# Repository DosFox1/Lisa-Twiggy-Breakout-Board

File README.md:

# Lisa-Twiggy-Breakout-Board
A fork of Roland Juno's original Lisa breakout board - now with Twiggy!

# So... What is it? 
This is a variant of RolandJunos original Lisa breakout board (https://github.com/RolandJuno/Lisa_Breakout), that includes an additional connector for the Lisa LITE. 
Adding the Lisa LITE connector will allow for 400K Floppy Drives to be connected to a Lisa.
This is because the Lisa LITE generates a PWM signal for the main drive motor in the 400K floppy drive. 
In a Macintosh, this PWM signal is generated by the ASG and audio interface! (I mean, I guess it's all PWM signals).

However, 800K drives and Floppy Emu generate their own PWM signal - so that pin is usually left disconnected. 
As a result, you can use a passive adapter for those drives.

Note, in the surprising event that you have an actual Twiggy Drive, please note this probably will not work.
This is because to two signals (sense and read) are tied together for the 800K drive. I felt a bit lazy and didn't add a way to keep these separate. 
If you have a Twiggy, cut and strap I guess? 

# Engineers Notes
The BOM remains the same as the original breakout board, except for the addition of a 26 pin shrouded connector for the Twiggy pinout.

**IMPORTANT:**

Do NOT connect a Twiggy/Lisa LITE at the same time as a Sony Drive. They share the same enable lines, and bad stuff (TM) is likely to happen. 
So don't do that. 

**Errata and other notes:**

* I've cleaned up some of the tracks and added thermal relief for soldering. 
* The errata for the 7905 footprint has been fixed (and added some silk to make sure the polarity is right!).
* AGND is also now connected to normal DGND, so no jumper is needed.
* Mounting holes have now been added (three in total), which are positioned in a line on the board. This will help with case building.
* To help with case building, the included SVGs are 1:1 scale to the actual board, meaning they can be imported into your favourite CAD program to help build a case around it.

**NOTE - This is Entirely Untested. Proceed With Caution**

It's best practise to power thsi adapter board with a bare (I.E, no IC's present) motherboard for intial testing.

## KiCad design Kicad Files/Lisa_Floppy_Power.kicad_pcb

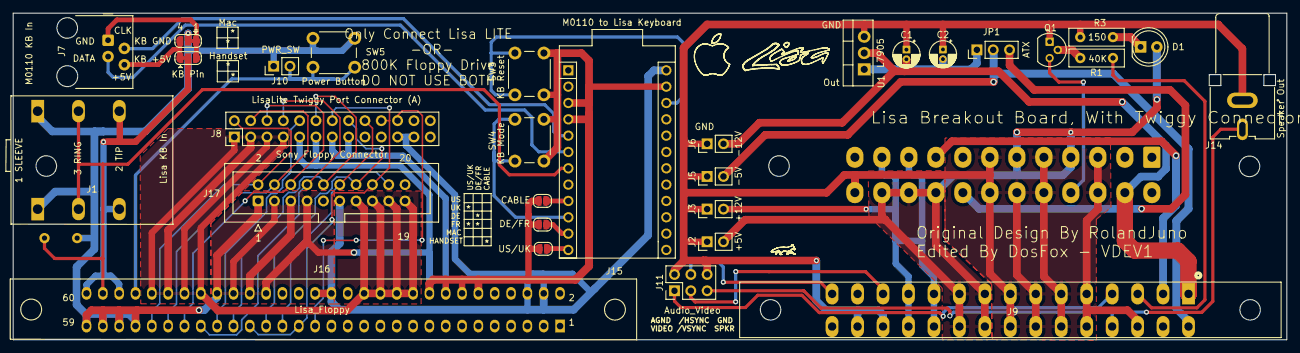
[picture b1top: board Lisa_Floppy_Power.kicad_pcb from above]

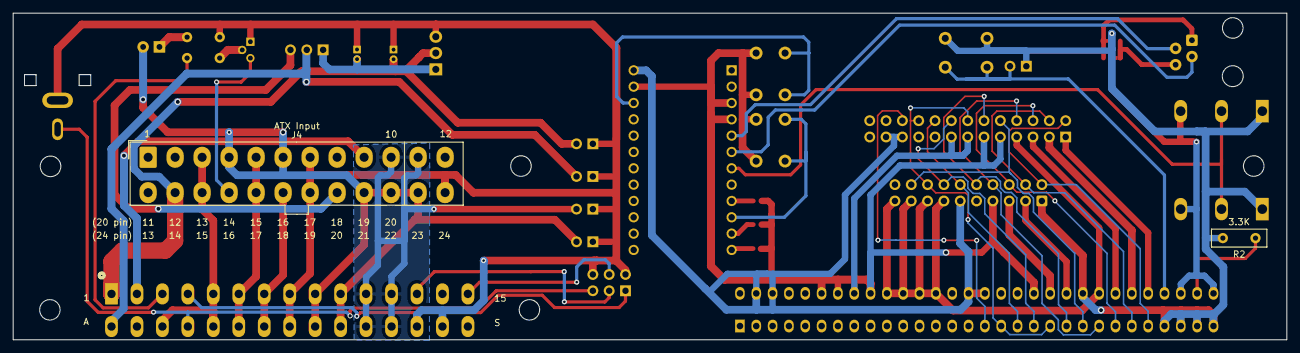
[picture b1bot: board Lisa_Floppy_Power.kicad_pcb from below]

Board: 2 copper layers, 198.1 x 50.8 mm, 32 parts (2 on the bottom side), 41 nets.

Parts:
C1, C2: 0.1uf; CP_Radial_D4.0mm_P1.50mm
D1: LED; LED_D5.0mm
J1: Lisa KB In; 0.25IN_STEREO_HEADPHONE_JACK
J2: +5V; PinHeader_1x02_P2.54mm_Vertical
J3: +12V; PinHeader_1x02_P2.54mm_Vertical
J4: ATX-24; Molex_Mini-Fit_Jr_5566-24A_2x12_P4.20mm_Vertical
J5: -5V; PinHeader_1x02_P2.54mm_Vertical
J6: -12V; PinHeader_1x02_P2.54mm_Vertical
J7: Mac_Plus_RJ9-4P4C; RJ9_Evercom_5301-440xxx_Horizontal
J8: LisaLite Twiggy Port Connector (A); PinHeader_2x13_P2.54mm_Vertical
J9: Lisa_Power_Video_Sound_Edge; Lisa Motherboard Power Edge
J10: PWR_SW; PinHeader_1x02_P2.54mm_Vertical
J11: Audio_Video; PinHeader_2x03_P2.54mm_Vertical
J14: Speaker Out; CUI_RCJ-047
J15: Arduino_Pro_Micro_5V_16MHz; Sparkfun_Pro_Micro
J16: Lisa_Floppy; 1-5530841-8_TE_CONN_60_DUAL_EDGE
J17: Sony Floppy Connector; IDC-Header_2x10_P2.54mm_Vertical
JP1: -5V_Selector; PinHeader_1x03_P2.54mm_Vertical
JP2: KB +5V; SolderJumper-3_P1.3mm_Bridged12_RoundedPad1.0x1.5mm
JP3: KB GND; SolderJumper-3_P1.3mm_Bridged12_RoundedPad1.0x1.5mm
JP4: US/UK; SolderJumper-2_P1.3mm_Open_RoundedPad1.0x1.5mm
JP5: DE/FR; SolderJumper-2_P1.3mm_Open_RoundedPad1.0x1.5mm
JP6: CABLE; SolderJumper-2_P1.3mm_Open_RoundedPad1.0x1.5mm
Q1: 2N4401BU; TO-92
R1: 40K; R_Box_L8.4mm_W2.5mm_P5.08mm
R2: 3.3K; R_Box_L8.4mm_W2.5mm_P5.08mm
R3: 150; R_Box_L8.4mm_W2.5mm_P5.08mm
SW3: KB Reset; SW_PUSH_6mm
SW4: KB Mode; SW_PUSH_6mm
SW5: Power Button; SW_PUSH_6mm
U1: L7905; TO-220-3_Vertical

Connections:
+5V: D1.2 (A), J2.2, J4.4 (+5V), J4.6 (+5V), J4.21 (+5V), J4.22 (+5V), J4.23 (+5V), J9.9, J9.10, J9.K, J9.L
+5VSB: J4.9 (+5VSB), J9.2
+5V_L: J8.21 (+5V), J8.23 (+5V), J15.24 (RAW), J16.4, J16.6, J16.30, J16.32, J17.11
+5V_L1: J1.2 (T), J16.56, J16.60, JP2.2 (C)
+12V-L: J8.1 (+12V), J8.3 (+12V), J8.5 (+12V), J8.7 (+12V), J16.20, J16.22, J16.24, J16.26, J16.46, J16.48, J16.50, J16.52, J17.13, J17.15, J17.17, J17.19
+12V-R: J3.2, J4.10 (+12V), J4.11 (+12V), J9.11, J9.12, J9.M, J9.N
-5V: J5.2, J9.A, JP1.2 (C)
-5V_7905: C2.2, JP1.1 (A), U1.1 (GND)
-5V_ATX: J4.20 (-5V), JP1.3 (B)
-12V: C1.2, J4.14 (-12V), J6.2, J9.1, U1.2 (VI)
CABLE: J15.9 (~D6/A7), JP6.2 (B)
DE/FR: J15.11 (D8/A8), JP5.2 (B)
GND-L: J1.1 (S), J8.9 (GND), J8.11 (GND), J8.13 (GND), J8.15 (GND), J10.1, J15.3 (GND), J15.4 (GND), J15.23 (GND), J16.12, J16.14, J16.16, J16.18, J16.38, J16.40, J16.42, J16.44, J16.53, J16.55, J16.57, J16.59, J17.1, J17.3, J17.5, J17.7, JP3.2 (C), JP4.1 (A), JP5.1 (A), JP6.1 (A), R2.2, SW3.1, SW4.1, SW5.1
GND-R: C1.1, C2.1, J2.1, J3.1, J4.3 (GND), J4.5 (GND), J4.7 (GND), J4.15 (GND), J4.17 (GND), J4.18 (GND), J4.19 (GND), J4.24 (GND), J5.1, J6.1, J9.5, J9.6, J9.7, J9.8, J9.C, J9.E, J9.F, J9.H, J9.J, J9.P, J9.R, J11.2, J11.6, J14.1, Q1.1 (E), R3.1, U1.3 (VO)
GND/VCC: J7.4, JP2.1 (A), JP3.3 (B)
HDS-A: J8.18 (HEADSEL), J16.35, J17.12
KBD: J1.3 (R), J15.7 (D4/A6), J16.58, R2.1
KBD_RESET: J15.22 (RST), SW3.2
M0110_CLK: J7.3, J15.6 (~D3)
M0110_DATA: J7.2, J15.5 (D2)
MOD: J15.10 (D7), SW4.2
MOTRCLK: J8.22 (MOTRCLK), J16.31
unnamed: D1.1 (K), R3.2
unnamed: Q1.2 (B), R1.2
ON/OFF: J9.3, R1.1
PH0-A: J8.2 (PH0), J16.51, J17.2
PH1-A: J8.4 (PH1), J16.49, J17.4
PH2-A: J8.6 (PH2), J16.47, J17.6
PH3-A: J8.8 (PH3), J16.45, J17.8
PS_ON: J4.16 (PS_ON#), Q1.3 (C)
PWRSW: J10.2, J16.54, SW5.2
RDA-A: J8.14 (RD), J8.20 (SENSE), J16.33, J16.39, J17.16
SPKR: J9.D, J11.5, J14.2
US/UK: J15.12 (~D9/A9), JP4.2 (B)
VCC/GND: J7.1, JP2.3 (B), JP3.1 (A)
VIDEO: J9.4, J11.1
WRD-A: J8.10 (WR), J16.43, J17.18
/DR1-A: J8.16 (/DRVSEL), J16.37, J17.14
/HSYNC: J9.15, J11.4
/VSYNC: J9.13, J11.3
/WRQ-A: J8.12 (/WREQ), J16.41, J17.10

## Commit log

2024-11-28 Add files via upload
    Added initial files
2024-11-29 Add files via upload
    Fixed 7905 pinout
2024-11-29 Add files via upload
    KiCad files with updated 7905 footprint
2024-11-29 Add files via upload
    Updated Images
